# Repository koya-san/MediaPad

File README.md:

# MediaPad
I am making a macropad under Hack Club. My goal with this macropad is to allow for dedicated macros for streaming and editing alongside a screen that states which OBS I am on.
The macropad is a 3x3 that used MX-style switches and a 128x32 OLED screen. Side note, some files are named StreamerPad, the old name I gave for this project that I would sometimes mix up with MediaPad :P

MediaPad

Schematic

PCB

Case

My case will case will come together with 4 screws.
BOM: Seeed XIAO RP2040, 9x 1N4148 Diodes, 9x MX-Style switches, 1x 0.91 inch OLED display, 9x white blank DSA keycaps, 4x M3x16mm screws, 4x M3x5mx4mm heatset inserts

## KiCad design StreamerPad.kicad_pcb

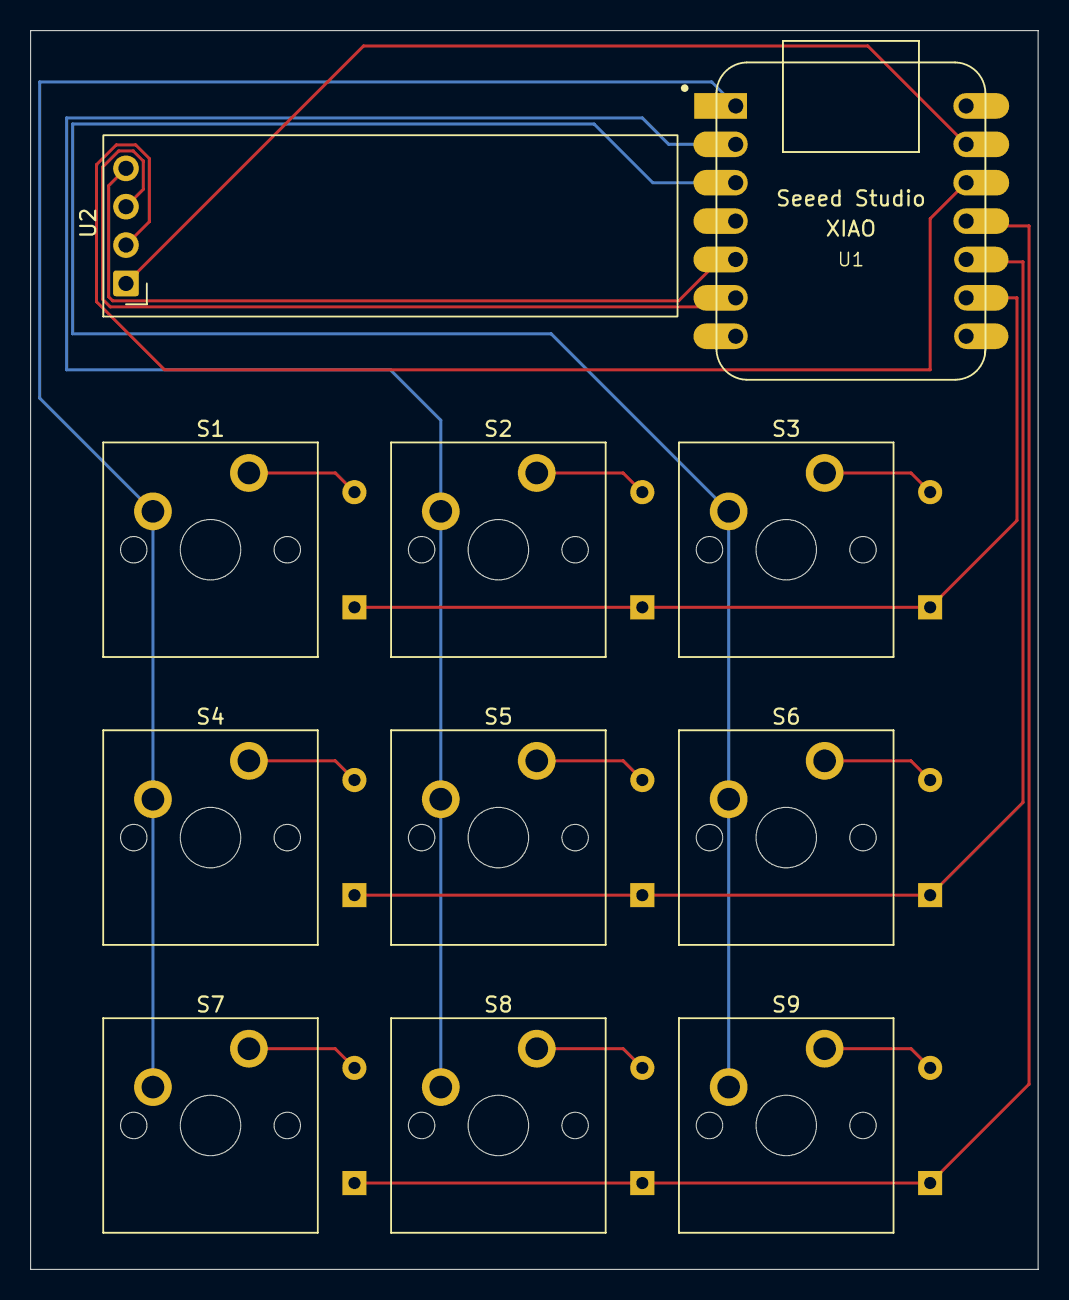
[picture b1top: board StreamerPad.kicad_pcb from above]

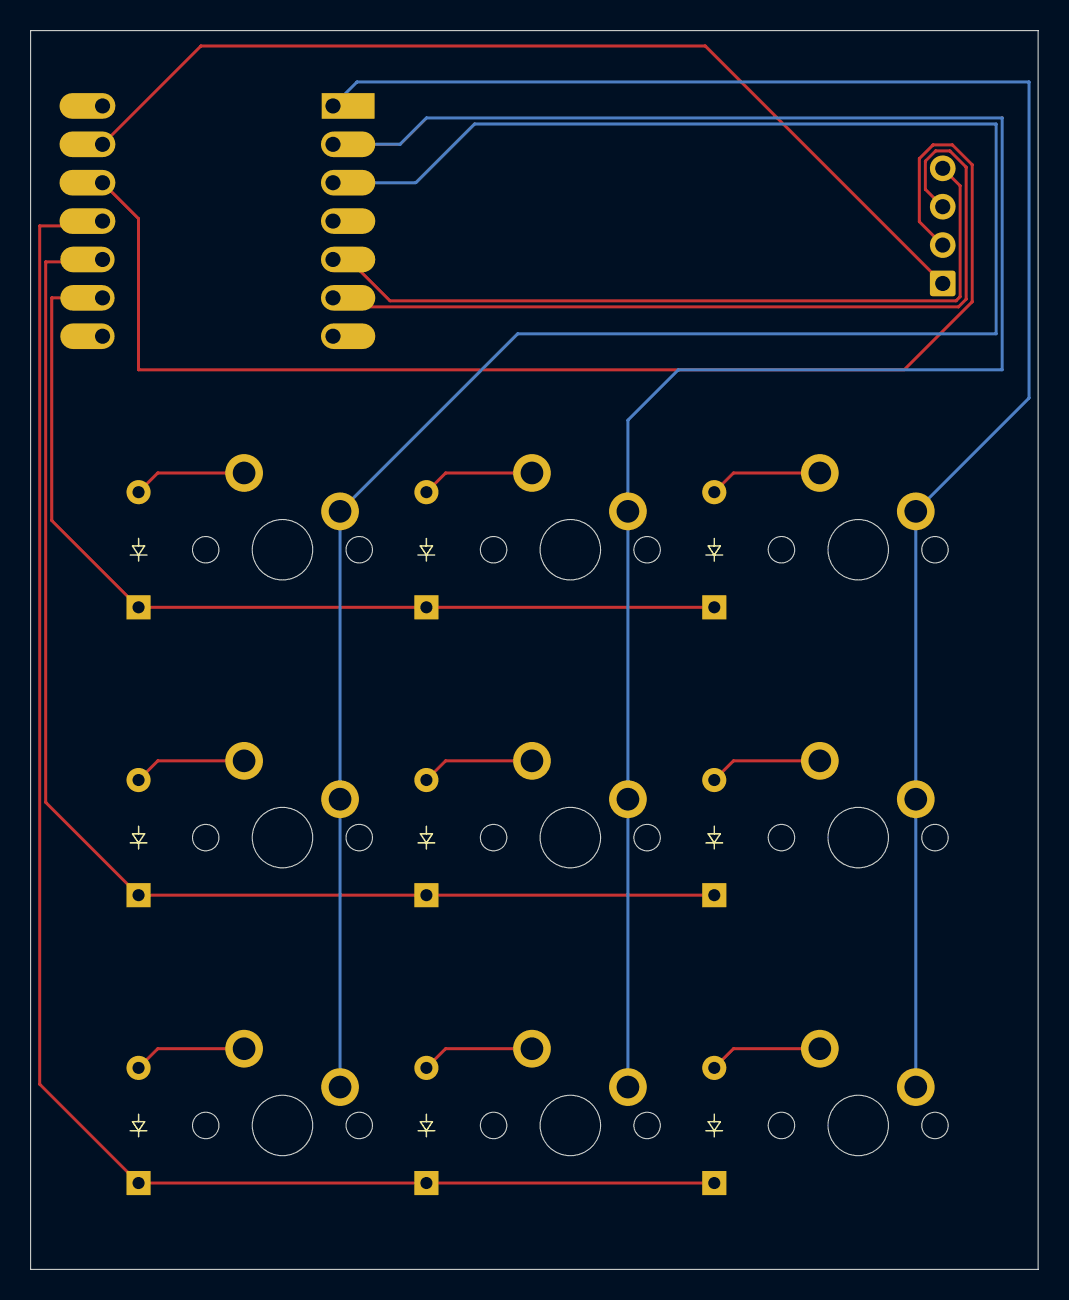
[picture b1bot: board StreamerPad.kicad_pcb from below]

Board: 2 copper layers, 66.7 x 82.0 mm, 20 parts (9 on the bottom side), 19 nets.

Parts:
D1, D2, D3, D4, D5, D6, D7, D8, D9: Diode_DO-35
S1, S2, S3, S4, S5, S6, S7, S8, S9: MX_PCB_1.00u
U1: MOUDLE-SEEEDUINO-XIAO; XIAO-Generic-Hybrid-14P-2.54-21X17.8MM
U2: ER_OLEDM0.91_1x-I2C

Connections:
Column 0: S1.1, S4.1, S7.1, U1.1 (PA02_A0_D0)
Column 1: S2.1, S5.1, S8.1, U1.2 (PA4_A1_D1)
Column 2: S3.1, S6.1, S9.1, U1.3 (PA10_A2_D2)
GND: U1.13 (GND), U2.1 (GND)
unnamed: D1.2 (A), S1.2
unnamed: D2.2 (A), S2.2
unnamed: D3.2 (A), S3.2
unnamed: D4.2 (A), S4.2
unnamed: D5.2 (A), S5.2
unnamed: D6.2 (A), S6.2
unnamed: D7.2 (A), S7.2
unnamed: D8.2 (A), S8.2
unnamed: D9.2 (A), S9.2
Row 0: D1.1 (K), D2.1 (K), D3.1 (K), U1.9 (PA7_A8_D8_SCK)
Row 1: D4.1 (K), D5.1 (K), D6.1 (K), U1.10 (PA5_A9_D9_MISO)
Row 2: D7.1 (K), D8.1 (K), D9.1 (K), U1.11 (PA6_A10_D10_MOSI)
SCL: U1.6 (PA9_A5_D5_SCL), U2.3 (SCL)
SDA: U1.5 (PA8_A4_D4_SDA), U2.4 (SDA)
VCC: U1.12 (3V3), U2.2 (VCC)
